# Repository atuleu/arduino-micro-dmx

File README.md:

# Arduino Micro DMX board

An arduino micro based DMX in/out board.

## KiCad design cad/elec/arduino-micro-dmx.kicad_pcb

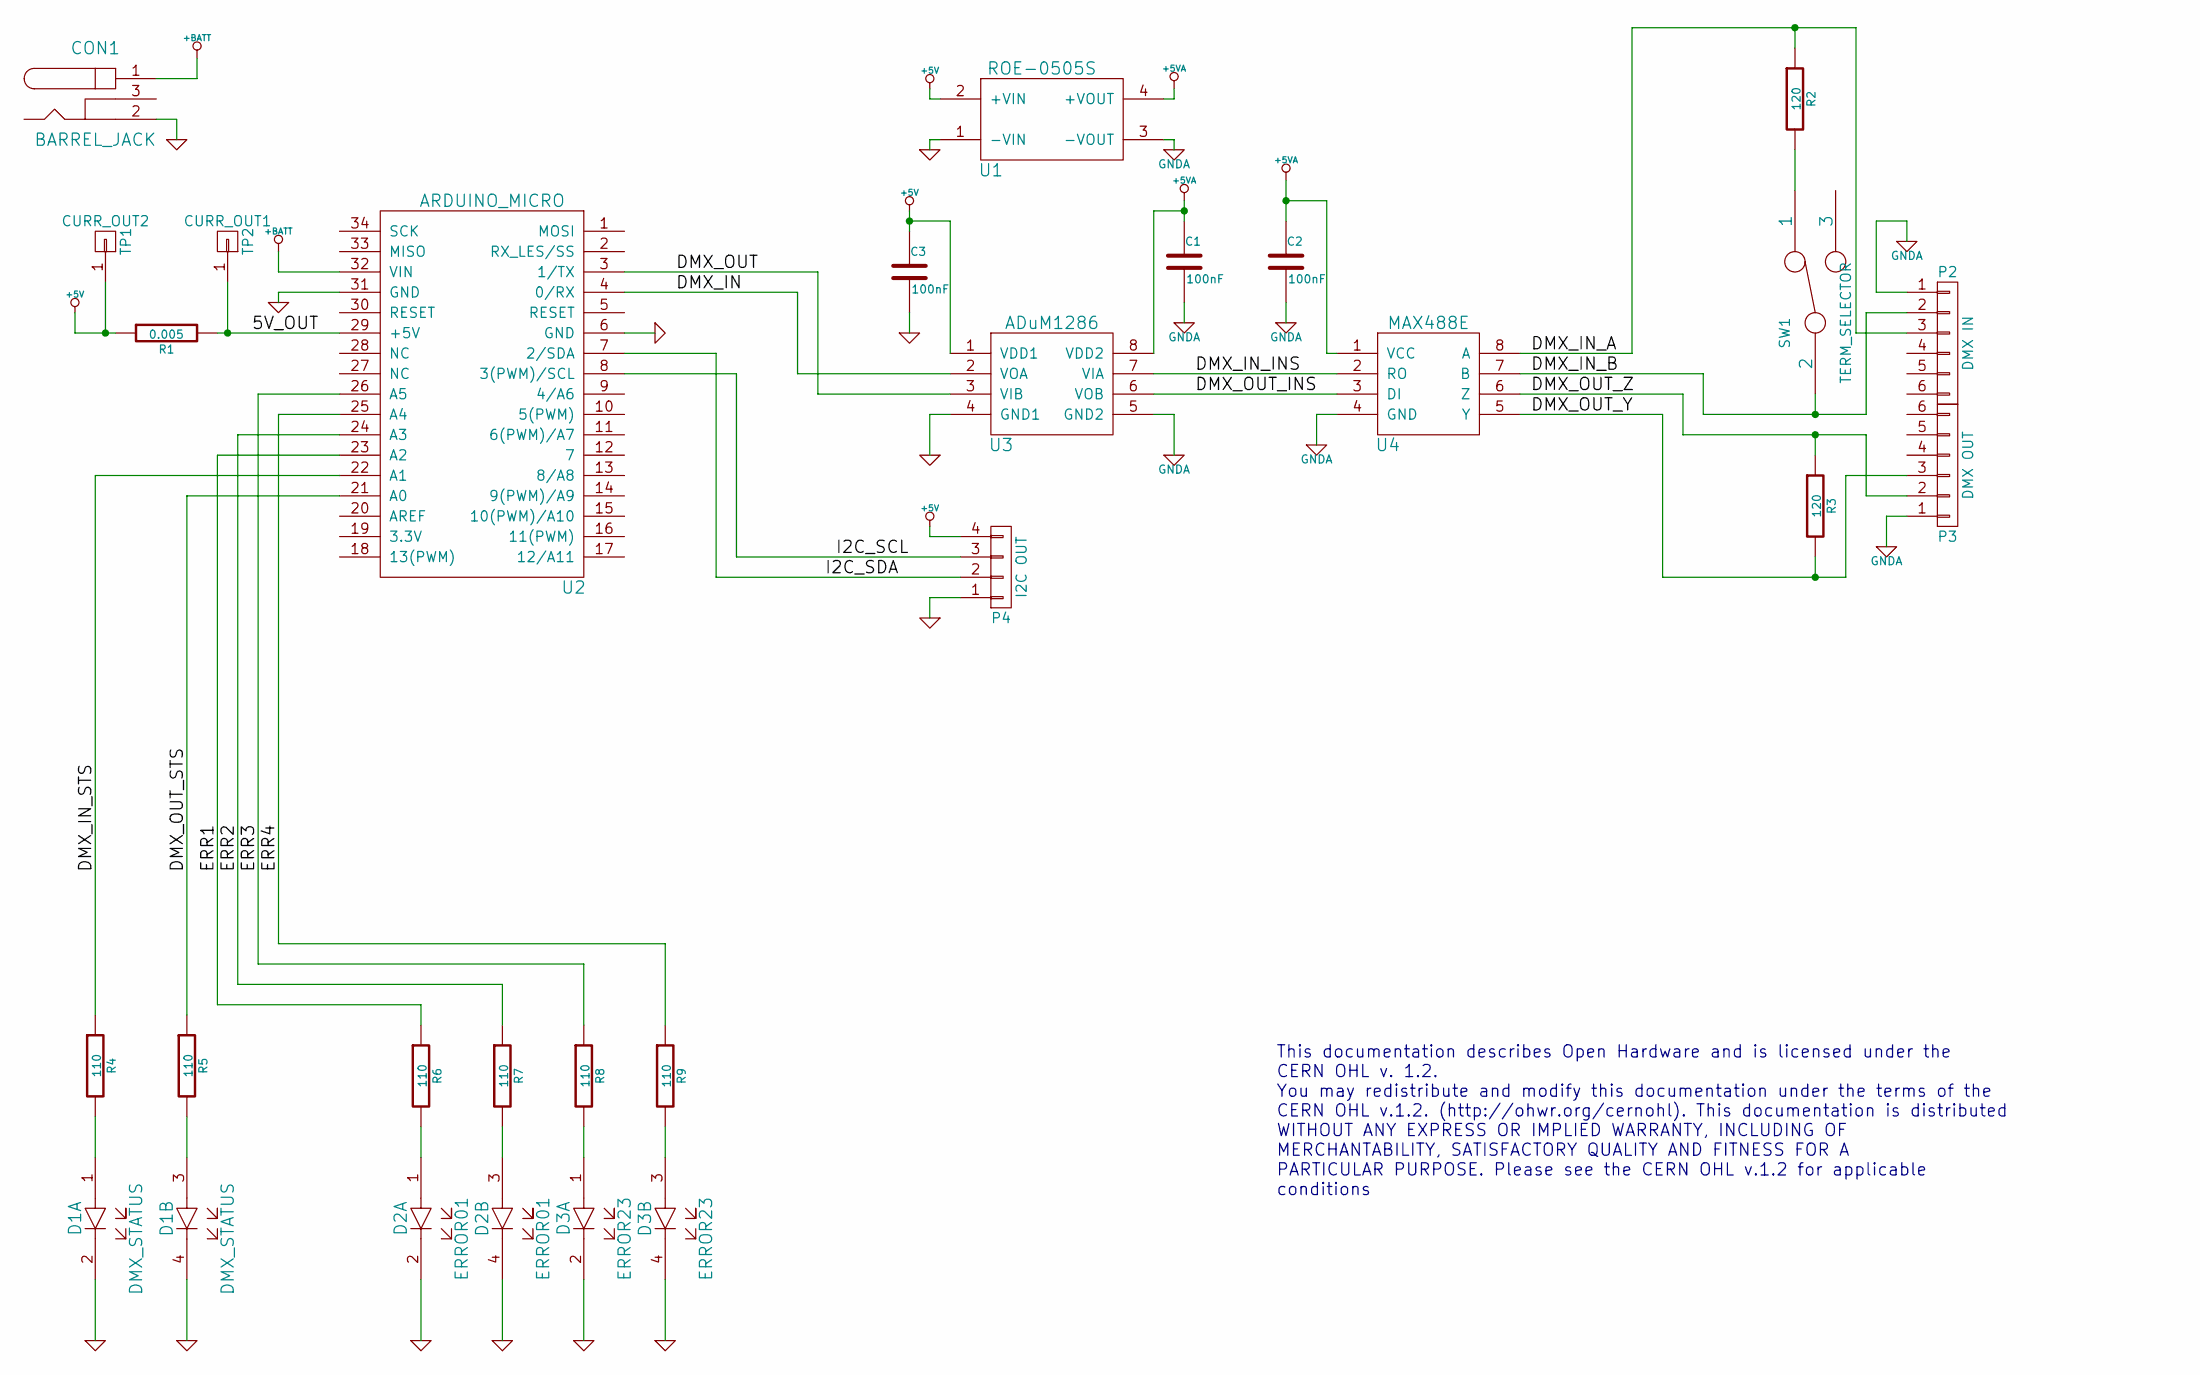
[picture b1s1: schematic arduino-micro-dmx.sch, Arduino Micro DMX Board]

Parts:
C1, C2, C3: 100nF; C_0805_HandSoldering; Part Number VJ0805Y104MXXAC
CON1: BARREL_JACK; RASM-712PX; Part Number RASM-712PX
D1: DMX_STATUS; SSF-LXG22573; Part Number SSF-LXH22573GGD
D2: ERROR01; SSF-LXG22573; Part Number SSF-LXH22573GGD
D3: ERROR23; SSF-LXG22573; Part Number SSF-LXH22573GGD
P2: DMX IN; NC5MBH; Part Number NC5MNH
P3: DMX OUT; NC5FBH; Part Number NC5FNH
P4: I2C OUT; Pin_Header_Angled_1x04
R1: 0.005; R_0805_HandSoldering; Part Number LRMAM0805-R005FT5
R2, R3: 120; R_0805_HandSoldering; Part Number RK73H2ATTD1200F
R4, R5, R6, R7, R8, R9: 110; R_0805_HandSoldering; Part Number RK73B2ATTD111J
SW1: TERM_SELECTOR; SSSS810701; Part Number SSSS810701
TP1: CURR_OUT2; PINTST
TP2: CURR_OUT1; PINTST
U1: ROE-0505S; Part Number ROE-0505S
U2: ARDUINO_MICRO; Part Number Arduino Micro
U3: ADuM1286; SOIC-8-N; Part Number ADUM1286ARZ
U4: MAX488E; SOIC-8-N; Part Number MAX488ECSA

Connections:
+5V: C3.1, P4.4, R1.1, TP1.1, U1.2 (+VIN), U3.1 (VDD1)
+5VA: C1.1, C2.1, U1.4 (+VOUT), U3.8 (VDD2), U4.1 (VCC)
+BATT: CON1.1, U2.32 (VIN)
/5V_OUT: R1.2, TP2.1, U2.29 (+5V)
/DMX_IN: U2.4 (0/RX), U3.2 (VOA)
/DMX_IN_A: P2.3, R2.1, U4.8 (A)
/DMX_IN_B: P2.2, SW1.2, U4.7 (B)
/DMX_IN_INS: U3.7 (VIA), U4.2 (RO)
/DMX_IN_STS: R4.1, U2.22 (A1)
/DMX_OUT: U2.3 (1/TX), U3.3 (VIB)
/DMX_OUT_INS: U3.6 (VOB), U4.3 (DI)
/DMX_OUT_STS: R5.1, U2.21 (A0)
/DMX_OUT_Y: P3.3, R3.2, U4.5 (Y)
/DMX_OUT_Z: P3.2, R3.1, U4.6 (Z)
/ERR1: R6.1, U2.23 (A2)
/ERR2: R7.1, U2.24 (A3)
/ERR3: R8.1, U2.26 (A5)
/ERR4: R9.1, U2.25 (A4)
/I2C_SCL: P4.3, U2.8 (3(PWM)/SCL)
/I2C_SDA: P4.2, U2.7 (2/SDA)
GND: C3.2, CON1.2, D1.2 (K), D1.4 (K), D2.2 (K), D2.4 (K), D3.2 (K), D3.4 (K), P4.1, U1.1 (-VIN), U2.6 (GND), U2.31 (GND), U3.4 (GND1)
GNDA: C1.2, C2.2, P2.1, P3.1, U1.3 (-VOUT), U3.5 (GND2), U4.4 (GND)
unnamed: D1.1 (A), R4.2
unnamed: D1.3 (A), R5.2
unnamed: D2.1 (A), R6.2
unnamed: D2.3 (A), R7.2
unnamed: D3.1 (A), R8.2
unnamed: D3.3 (A), R9.2
unnamed: R2.2, SW1.1

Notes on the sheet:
This documentation describes Open Hardware and is licensed under the CERN OHL v. 1.2. You may redistribute and modify this documentation under the terms of the CERN OHL v.1.2. (http://ohwr.org/cernohl). This documentation is distributed WITHOUT ANY EXPRESS OR IMPLIED WARRANTY, INCLUDING OF MERCHANT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

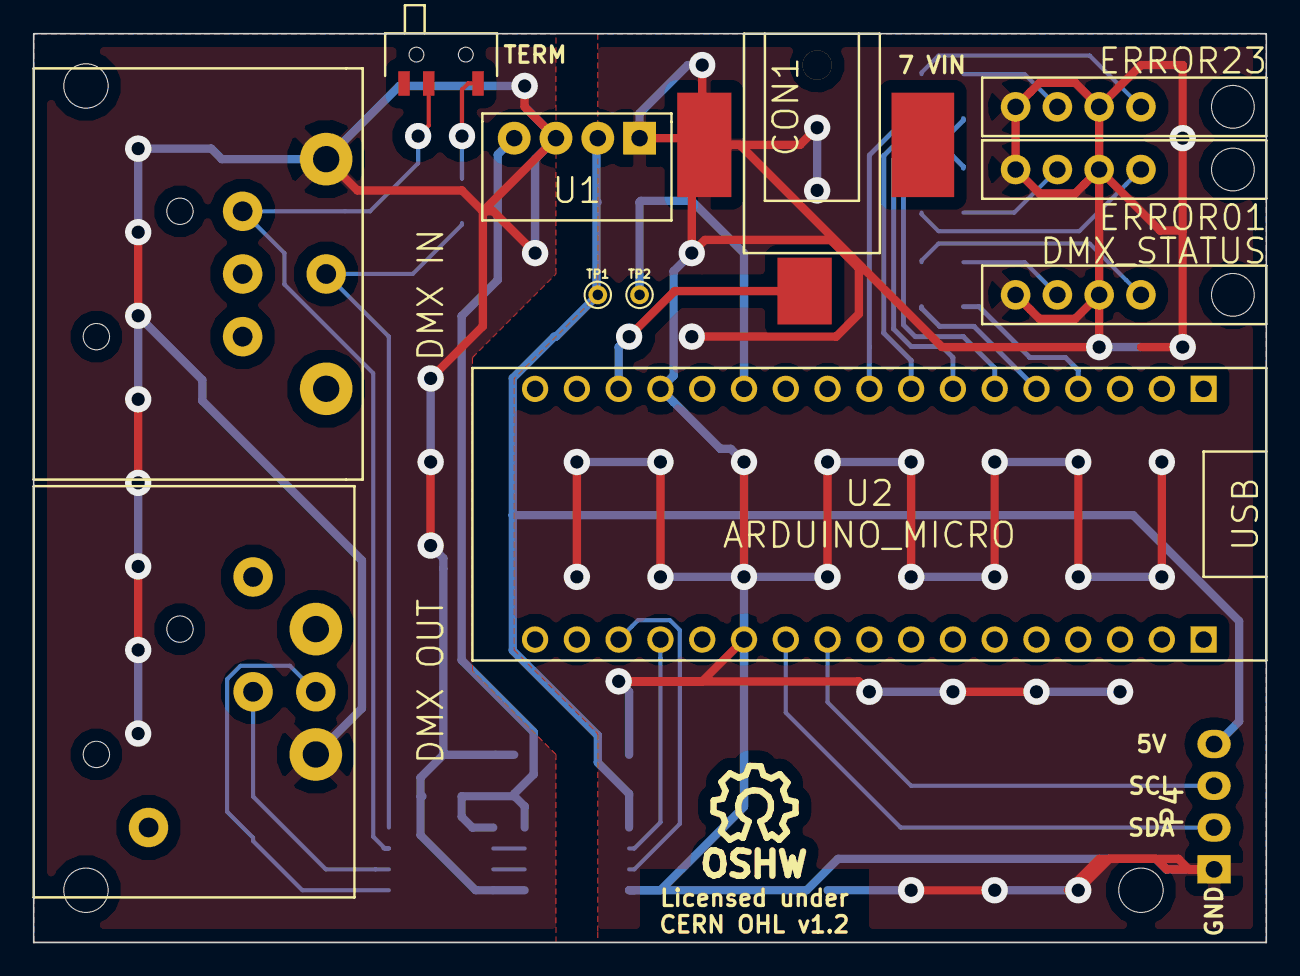
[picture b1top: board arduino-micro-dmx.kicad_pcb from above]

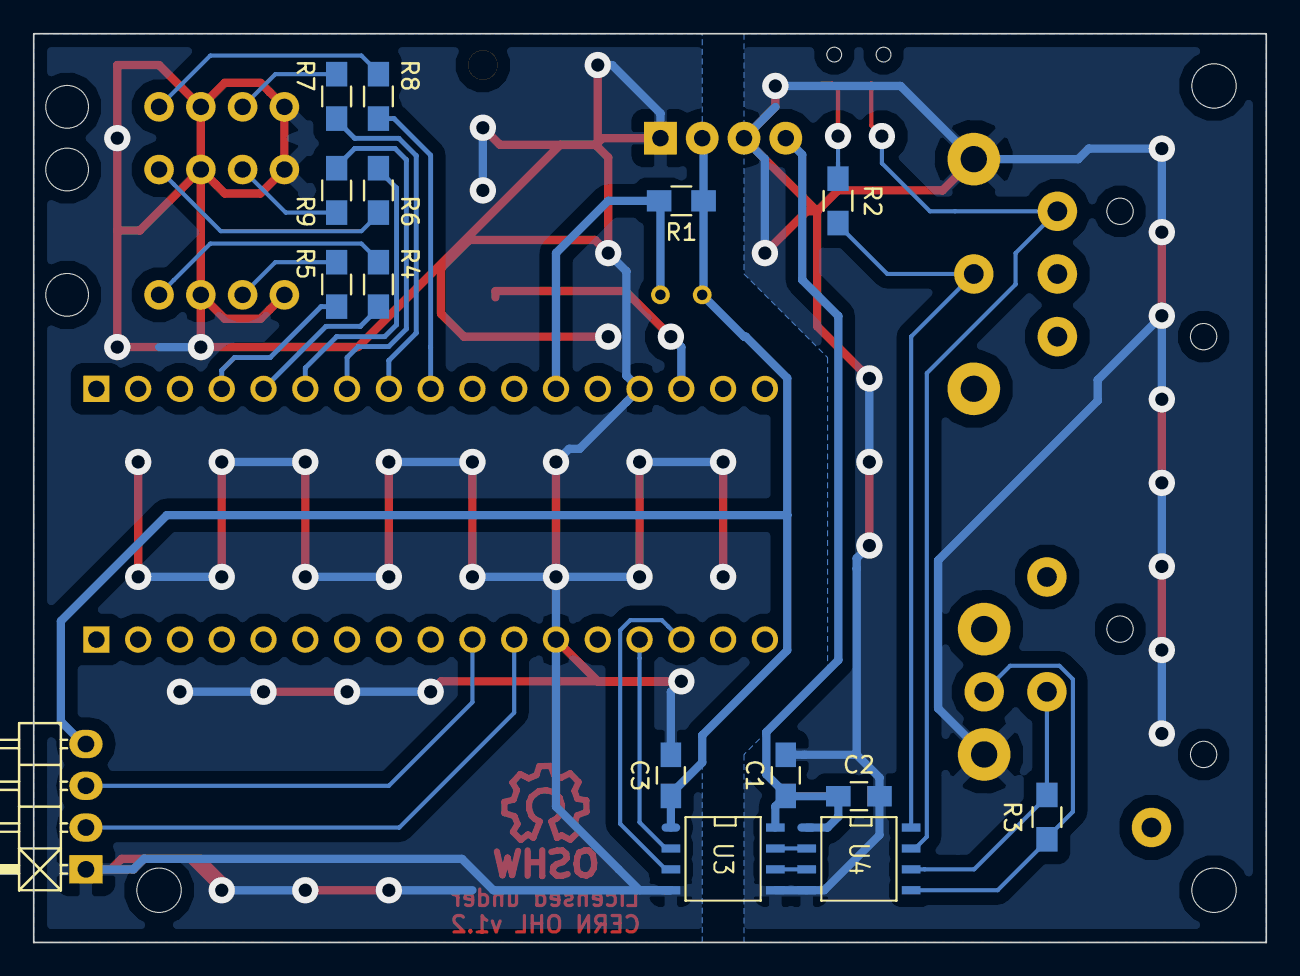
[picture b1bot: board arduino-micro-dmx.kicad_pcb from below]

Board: 2 copper layers, 74.9 x 55.2 mm, 31 parts (15 on the bottom side), 29 nets.

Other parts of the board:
MH: MountingHole_2-7mm_RevA_Date21Jun2010; MountingHole_2-7mm
MH#2, MH#3: MountingHole_2-7mm_RevA_Date21Jun2010; MountingHole_2-7mm
SYM: Symbol_OSHW-Logo_CopperTop_07Jul2012; Symbol_OSHW-Logo_CopperTop
SYM#2: Symbol_OSHW-Logo_SilkScreen_07Jul2012; Symbol_OSHW-Logo_SilkScreen

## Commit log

2014-11-19 Initial commit with license information
2014-11-19 Adds a first version of the schematics
2014-11-20 Connects arduino I/O
2014-11-20 first routing
2014-11-21 Polishing

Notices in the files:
cad/elec/arduino-micro-dmx.kicad_pcb:
Copyright 2014 (c) Alexandre Tuleu
Licensed under CERN OHL v 1.2 or Later
